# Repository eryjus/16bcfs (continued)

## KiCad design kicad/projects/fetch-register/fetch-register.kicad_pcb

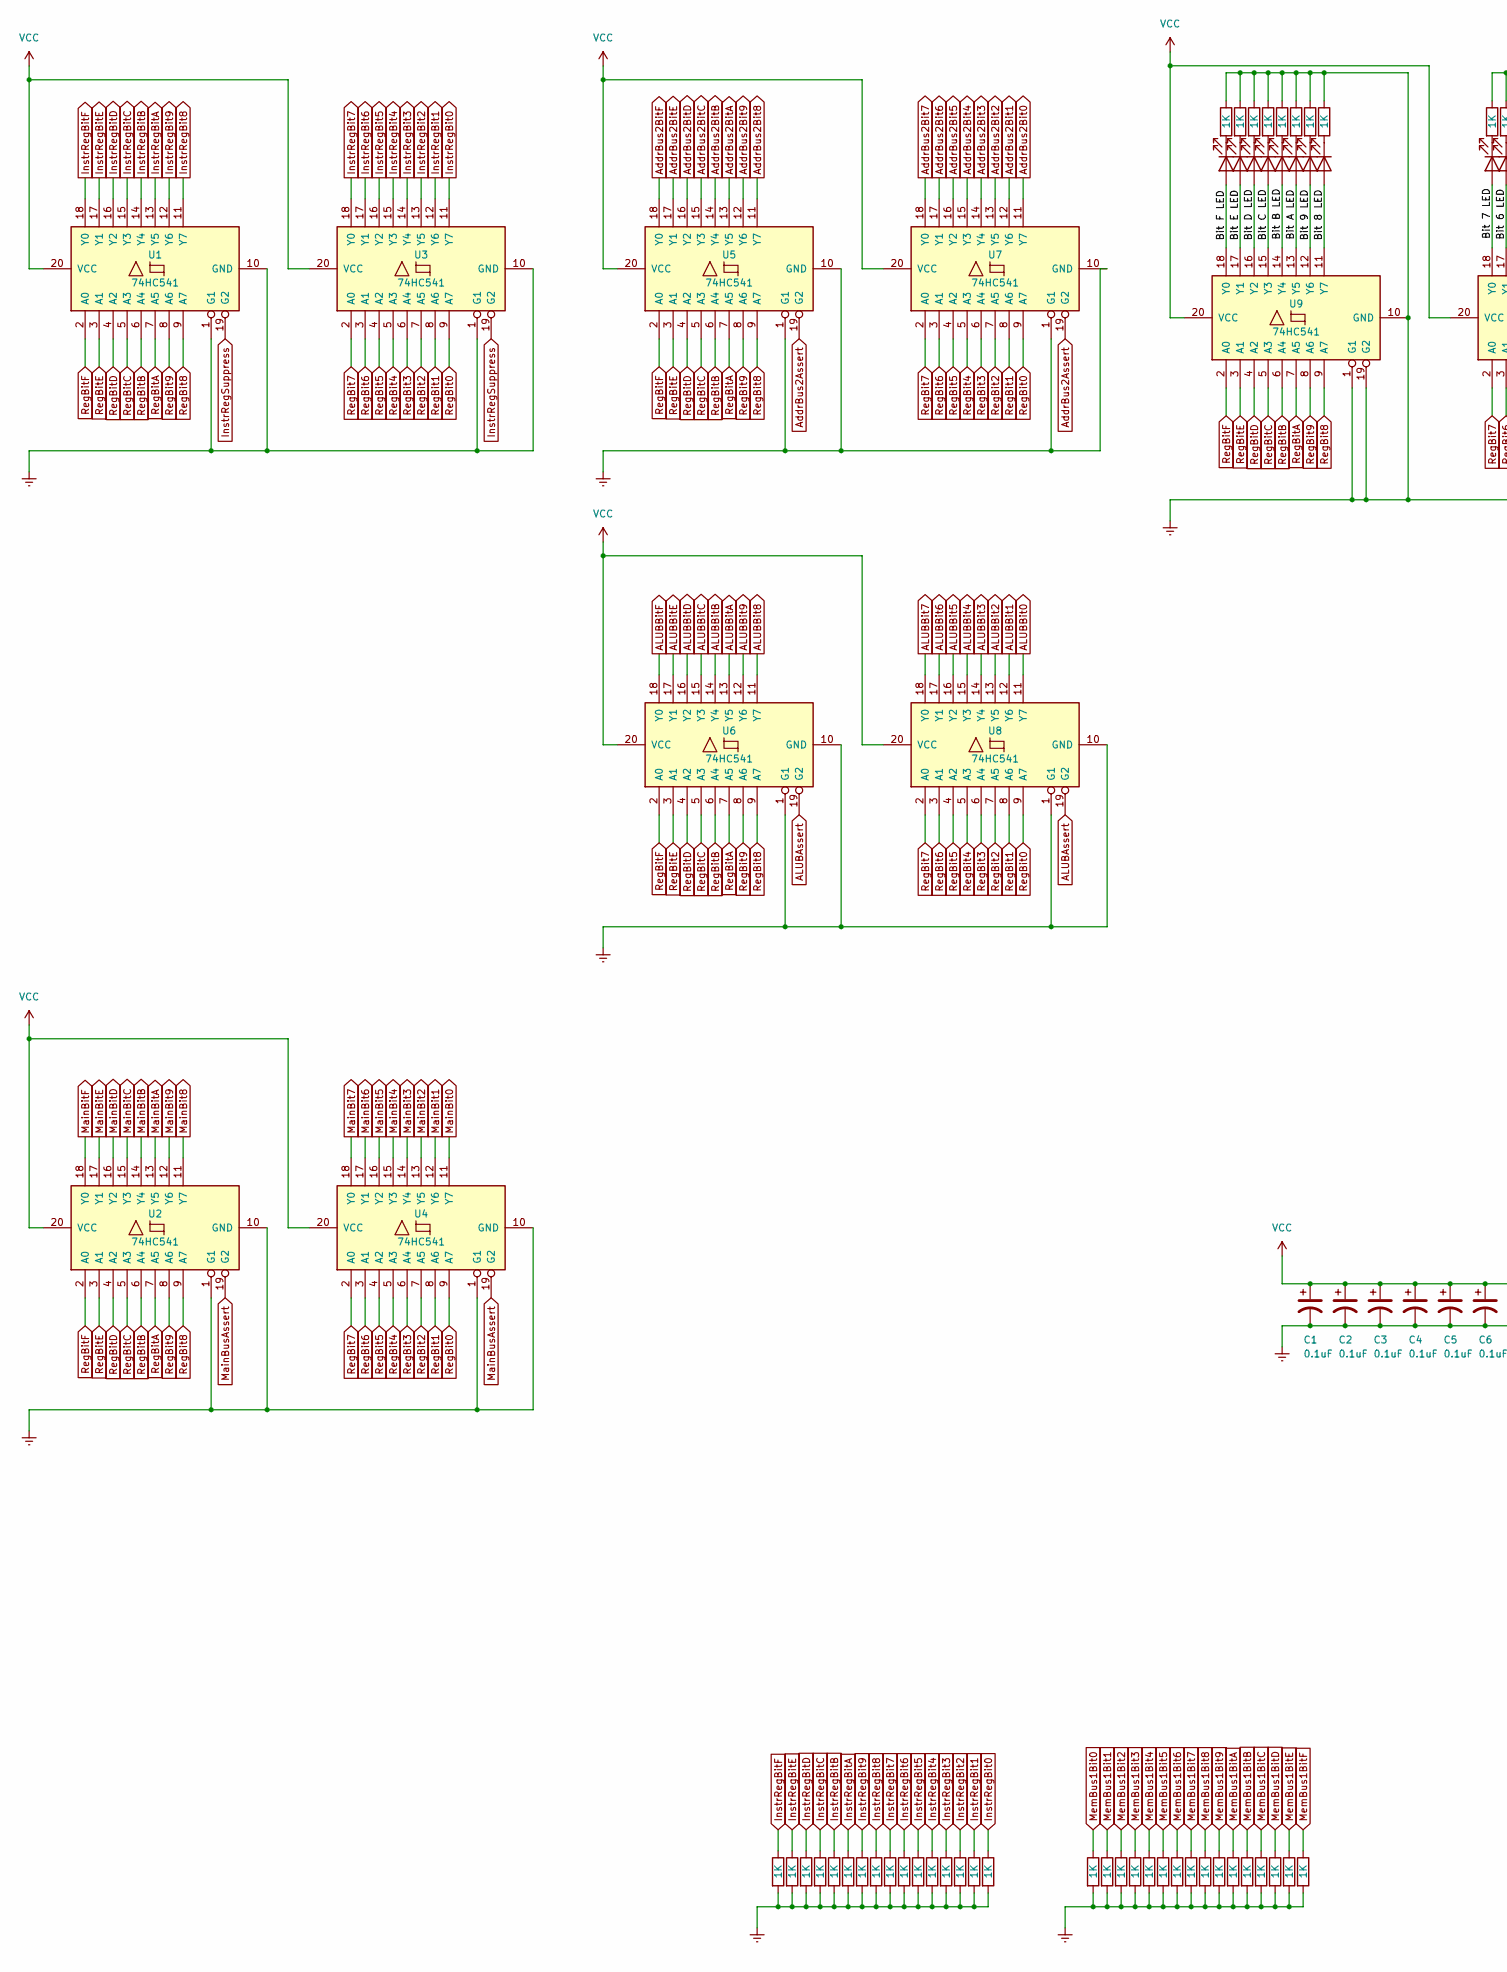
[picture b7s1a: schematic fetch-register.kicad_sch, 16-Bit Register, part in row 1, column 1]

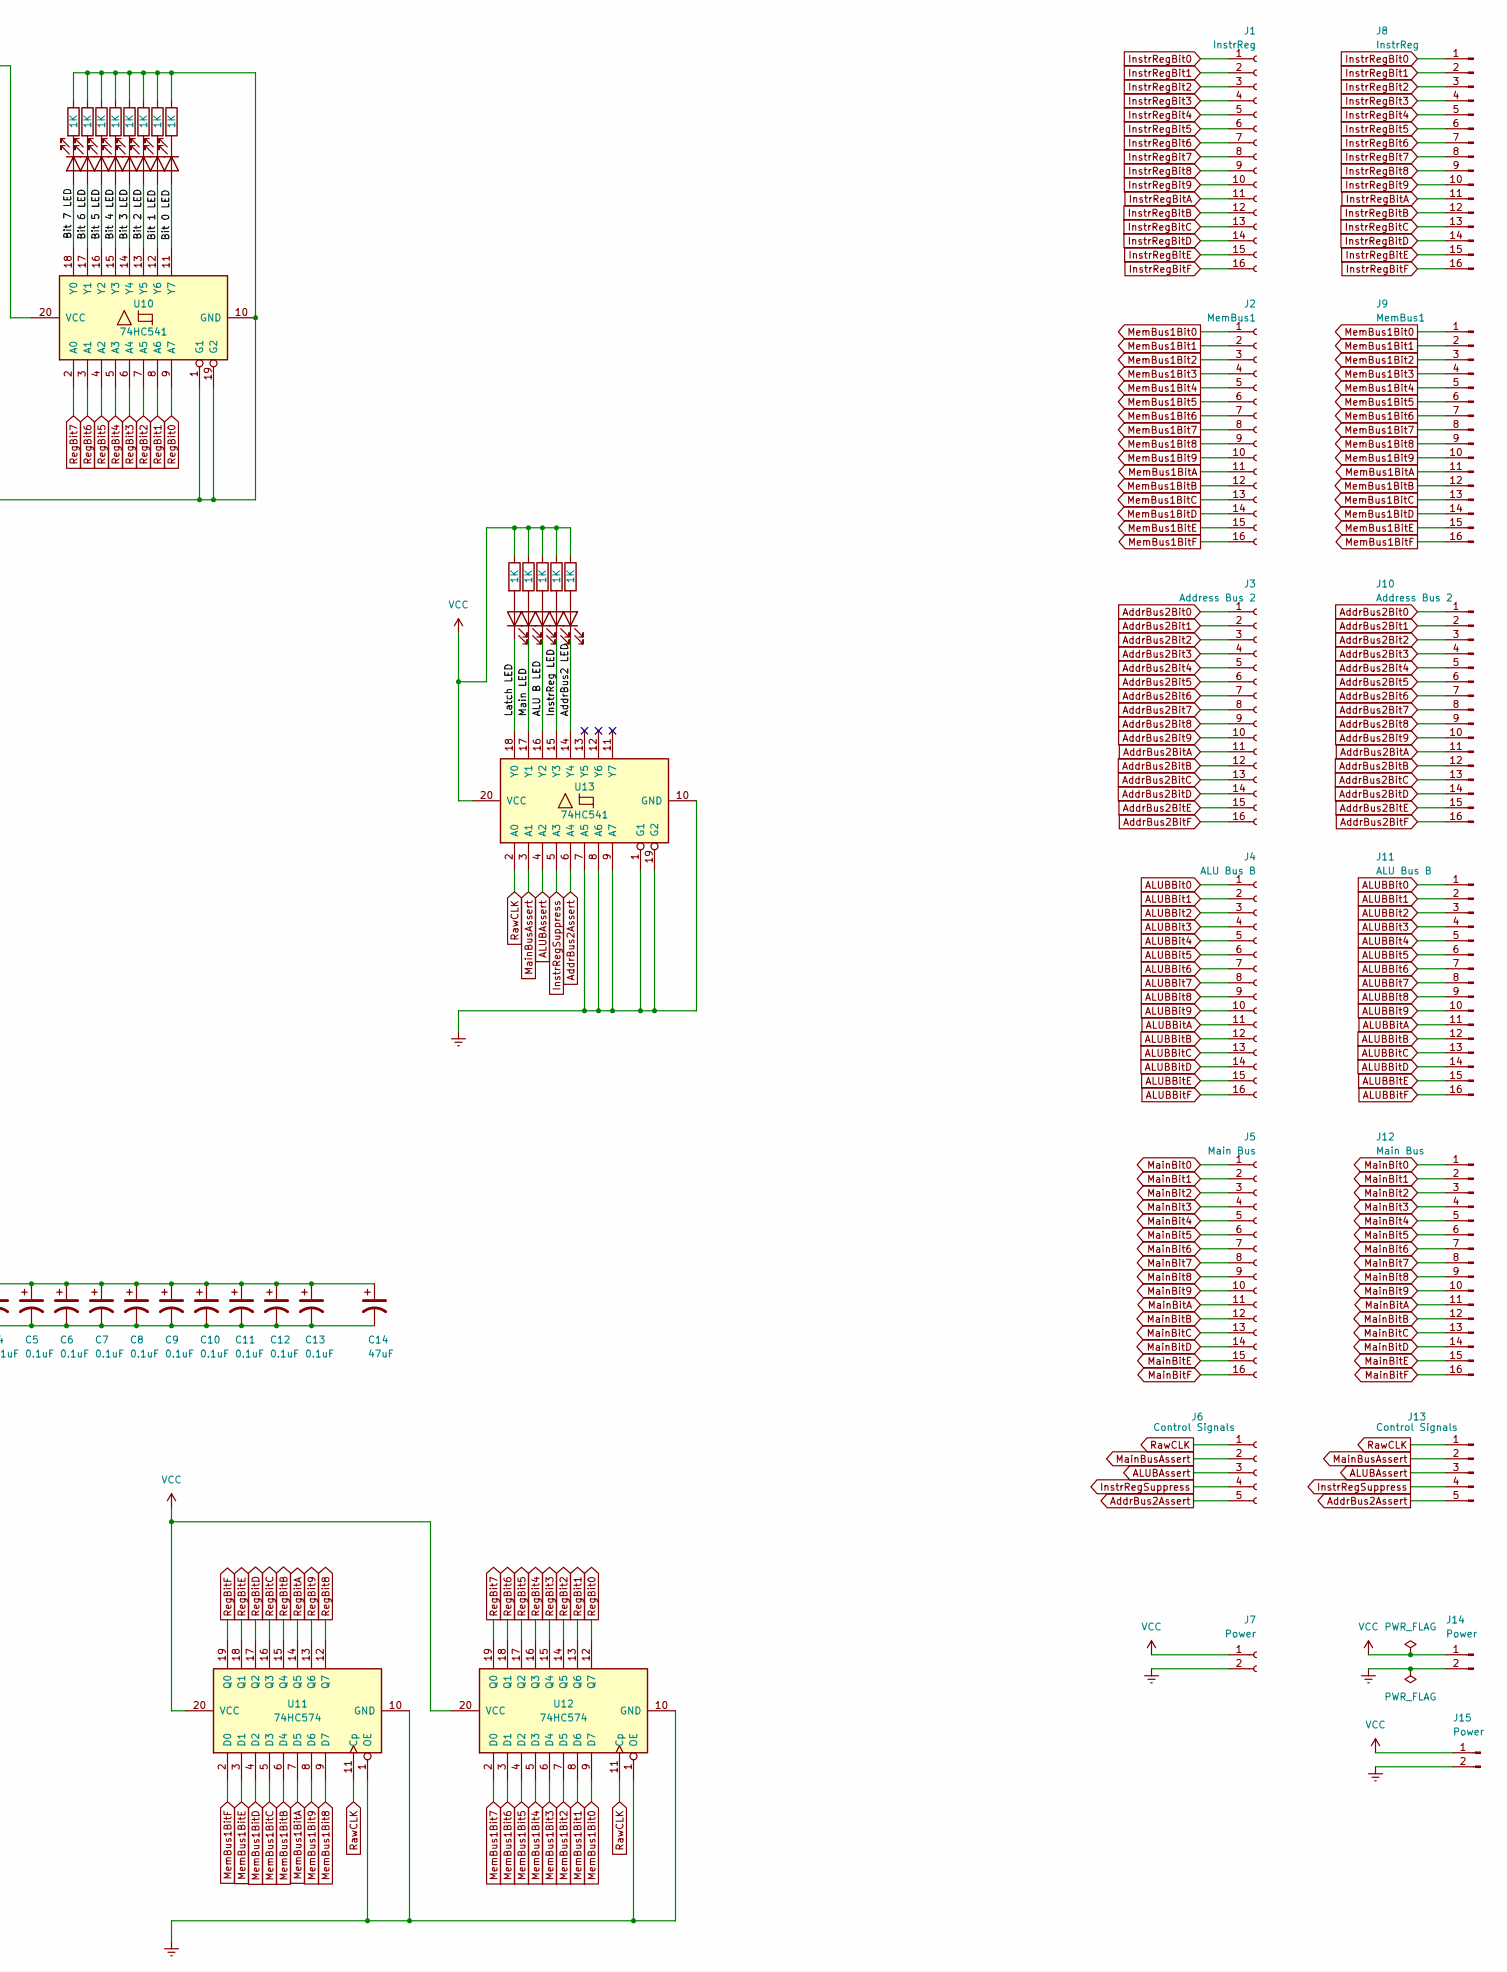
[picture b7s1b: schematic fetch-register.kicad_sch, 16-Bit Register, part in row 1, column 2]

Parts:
C1, C2, C3, C4, C5, C6, C7, C8, C9, C10, C11, C12, C13: 0.1uF; C_1206_3216Metric_Pad1.33x1.80mm_HandSolder
C14: 47uF; C_1206_3216Metric_Pad1.33x1.80mm_HandSolder
D1, D2, D3, D4, D5, D6, D7, D8, D9, D10, D11, D12, D13, D14, D15, D16: Green; LED_1206_3216Metric_Pad1.42x1.75mm_HandSolder
D17, D18, D19, D20, D21: Red; LED_1206_3216Metric_Pad1.42x1.75mm_HandSolder
J1: InstrReg; PinSocket_1x16_P2.54mm_Vertical
J2: MemBus1; PinSocket_1x16_P2.54mm_Vertical
J3: Address Bus 2; PinSocket_1x16_P2.54mm_Vertical
J4: ALU Bus B; PinSocket_1x16_P2.54mm_Vertical
J5: Main Bus; PinSocket_1x16_P2.54mm_Vertical
J6: Control Signals; PinSocket_1x05_P2.54mm_Vertical
J7: Power; PinSocket_1x02_P2.54mm_Vertical
J8: InstrReg; PinHeader_1x16_P2.54mm_Vertical
J9: MemBus1; PinHeader_1x16_P2.54mm_Vertical
J10: Address Bus 2; PinHeader_1x16_P2.54mm_Vertical
J11: ALU Bus B; PinHeader_1x16_P2.54mm_Vertical
J12: Main Bus; PinHeader_1x16_P2.54mm_Vertical
J13: Control Signals; PinHeader_1x05_P2.54mm_Vertical
J14, J15: Power; PinHeader_1x02_P2.54mm_Vertical
R1, R2, R3, R4, R5, R6, R7, R8, R9, R10, R11, R12, R13, R14, R15, R16, R17, R18, R19, R20, R21, R22, R23, R24, R25, R26, R27, R28, R29, R30, R31, R32, R33, R34, R35, R36, R37, R38, R39, R40, R41, R42, R43, R44, R45, R46, R47, R48, R49, R50, R51, R52, R53: 1K; R_1206_3216Metric_Pad1.30x1.75mm_HandSolder
U1, U2, U3, U4, U5, U6, U7, U8, U9, U10, U13: 74HC541; SOIC-20W_7.5x12.8mm_P1.27mm
U11, U12: 74HC574; SOIC-20W_7.5x12.8mm_P1.27mm

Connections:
/ALU B LED: D19.1 (K), U13.16 (Y2)
/AddrBus2 LED: D21.1 (K), U13.14 (Y4)
/Bit 0 LED: D16.2 (A), U10.11 (Y7)
/Bit 1 LED: D15.2 (A), U10.12 (Y6)
/Bit 2 LED: D14.2 (A), U10.13 (Y5)
/Bit 3 LED: D13.2 (A), U10.14 (Y4)
/Bit 4 LED: D12.2 (A), U10.15 (Y3)
/Bit 5 LED: D11.2 (A), U10.16 (Y2)
/Bit 6 LED: D10.2 (A), U10.17 (Y1)
/Bit 7 LED: D9.2 (A), U10.18 (Y0)
/Bit 8 LED: D8.2 (A), U9.11 (Y7)
/Bit 9 LED: D7.2 (A), U9.12 (Y6)
/Bit A LED: D6.2 (A), U9.13 (Y5)
/Bit B LED: D5.2 (A), U9.14 (Y4)
/Bit C LED: D4.2 (A), U9.15 (Y3)
/Bit D LED: D3.2 (A), U9.16 (Y2)
/Bit E LED: D2.2 (A), U9.17 (Y1)
/Bit F LED: D1.2 (A), U9.18 (Y0)
/InstrReg LED: D20.1 (K), U13.15 (Y3)
/Latch LED: D17.1 (K), U13.18 (Y0)
/Main LED: D18.1 (K), U13.17 (Y1)
ALUBAssert: J6.3, J13.3, U6.19 (G2), U8.19 (G2), U13.4 (A2)
ALUBBit0: J4.1, J11.1, U8.11 (Y7)
ALUBBit1: J4.2, J11.2, U8.12 (Y6)
ALUBBit2: J4.3, J11.3, U8.13 (Y5)
ALUBBit3: J4.4, J11.4, U8.14 (Y4)
ALUBBit4: J4.5, J11.5, U8.15 (Y3)
ALUBBit5: J4.6, J11.6, U8.16 (Y2)
ALUBBit6: J4.7, J11.7, U8.17 (Y1)
ALUBBit7: J4.8, J11.8, U8.18 (Y0)
ALUBBit8: J4.9, J11.9, U6.11 (Y7)
ALUBBit9: J4.10, J11.10, U6.12 (Y6)
ALUBBitA: J4.11, J11.11, U6.13 (Y5)
ALUBBitB: J4.12, J11.12, U6.14 (Y4)
ALUBBitC: J4.13, J11.13, U6.15 (Y3)
ALUBBitD: J4.14, J11.14, U6.16 (Y2)
ALUBBitE: J4.15, J11.15, U6.17 (Y1)
ALUBBitF: J4.16, J11.16, U6.18 (Y0)
AddrBus2Assert: J6.5, J13.5, U5.19 (G2), U7.19 (G2), U13.6 (A4)
AddrBus2Bit0: J3.1, J10.1, U7.11 (Y7)
AddrBus2Bit1: J3.2, J10.2, U7.12 (Y6)
AddrBus2Bit2: J3.3, J10.3, U7.13 (Y5)
AddrBus2Bit3: J3.4, J10.4, U7.14 (Y4)
AddrBus2Bit4: J3.5, J10.5, U7.15 (Y3)
AddrBus2Bit5: J3.6, J10.6, U7.16 (Y2)
AddrBus2Bit6: J3.7, J10.7, U7.17 (Y1)
AddrBus2Bit7: J3.8, J10.8, U7.18 (Y0)
AddrBus2Bit8: J3.9, J10.9, U5.11 (Y7)
AddrBus2Bit9: J3.10, J10.10, U5.12 (Y6)
AddrBus2BitA: J3.11, J10.11, U5.13 (Y5)
AddrBus2BitB: J3.12, J10.12, U5.14 (Y4)
AddrBus2BitC: J3.13, J10.13, U5.15 (Y3)
AddrBus2BitD: J3.14, J10.14, U5.16 (Y2)
AddrBus2BitE: J3.15, J10.15, U5.17 (Y1)
AddrBus2BitF: J3.16, J10.16, U5.18 (Y0)
GNDREF: C1.2, C2.2, C3.2, C4.2, C5.2, C6.2, C7.2, C8.2, C9.2, C10.2, C11.2, C12.2, C13.2, C14.2, J7.2, J14.2, J15.2, R1.2, R2.2, R3.2, R4.2, R5.2, R6.2, R7.2, R8.2, R9.2, R10.2, R11.2, R12.2, R13.2, R14.2, R15.2, R16.2, R17.2, R18.2, R19.2, R20.2, R21.2, R22.2, R23.2, R24.2, R25.2, R26.2, R27.1, R28.2, R29.1, R30.2, R31.1, R32.2, R33.1, R34.2, R35.1, R36.2, R37.1, R38.2, R39.1, R40.1, R41.1, R42.1, R43.1, R44.1, R45.1, R46.1, R47.1, R48.1, U1.1 (G1), U1.10 (GND), U2.1 (G1), U2.10 (GND), U3.1 (G1), U3.10 (GND), U4.1 (G1), U4.10 (GND), U5.1 (G1), U5.10 (GND), U6.1 (G1), U6.10 (GND), U7.1 (G1), U7.10 (GND), U8.1 (G1), U8.10 (GND), U9.1 (G1), U9.10 (GND), U9.19 (G2), U10.1 (G1), U10.10 (GND), U10.19 (G2), U11.1 (OE), U11.10 (GND), U12.1 (OE), U12.10 (GND), U13.1 (G1), U13.7 (A5), U13.8 (A6), U13.9 (A7), U13.10 (GND), U13.19 (G2)
InstrRegBit0: J1.1, J8.1, R16.1, U3.11 (Y7)
InstrRegBit1: J1.2, J8.2, R15.1, U3.12 (Y6)
InstrRegBit2: J1.3, J8.3, R14.1, U3.13 (Y5)
InstrRegBit3: J1.4, J8.4, R13.1, U3.14 (Y4)
InstrRegBit4: J1.5, J8.5, R12.1, U3.15 (Y3)
InstrRegBit5: J1.6, J8.6, R11.1, U3.16 (Y2)
InstrRegBit6: J1.7, J8.7, R10.1, U3.17 (Y1)
InstrRegBit7: J1.8, J8.8, R9.1, U3.18 (Y0)
InstrRegBit8: J1.9, J8.9, R8.1, U1.11 (Y7)
InstrRegBit9: J1.10, J8.10, R7.1, U1.12 (Y6)
InstrRegBitA: J1.11, J8.11, R6.1, U1.13 (Y5)
InstrRegBitB: J1.12, J8.12, R5.1, U1.14 (Y4)
InstrRegBitC: J1.13, J8.13, R4.1, U1.15 (Y3)
InstrRegBitD: J1.14, J8.14, R3.1, U1.16 (Y2)
InstrRegBitE: J1.15, J8.15, R2.1, U1.17 (Y1)
InstrRegBitF: J1.16, J8.16, R1.1, U1.18 (Y0)
InstrRegSuppress: J6.4, J13.4, U1.19 (G2), U3.19 (G2), U13.5 (A3)
MainBit0: J5.1, J12.1, U4.11 (Y7)
MainBit1: J5.2, J12.2, U4.12 (Y6)
MainBit2: J5.3, J12.3, U4.13 (Y5)
MainBit3: J5.4, J12.4, U4.14 (Y4)
MainBit4: J5.5, J12.5, U4.15 (Y3)
MainBit5: J5.6, J12.6, U4.16 (Y2)
MainBit6: J5.7, J12.7, U4.17 (Y1)
MainBit7: J5.8, J12.8, U4.18 (Y0)
MainBit8: J5.9, J12.9, U2.11 (Y7)
MainBit9: J5.10, J12.10, U2.12 (Y6)
MainBitA: J5.11, J12.11, U2.13 (Y5)
MainBitB: J5.12, J12.12, U2.14 (Y4)
MainBitC: J5.13, J12.13, U2.15 (Y3)
MainBitD: J5.14, J12.14, U2.16 (Y2)
MainBitE: J5.15, J12.15, U2.17 (Y1)
MainBitF: J5.16, J12.16, U2.18 (Y0)
MainBusAssert: J6.2, J13.2, U2.19 (G2), U4.19 (G2), U13.3 (A1)
MemBus1Bit0: J2.1, J9.1, R17.1, U12.9 (D7)
MemBus1Bit1: J2.2, J9.2, R18.1, U12.8 (D6)
MemBus1Bit2: J2.3, J9.3, R19.1, U12.7 (D5)
MemBus1Bit3: J2.4, J9.4, R20.1, U12.6 (D4)
MemBus1Bit4: J2.5, J9.5, R21.1, U12.5 (D3)
MemBus1Bit5: J2.6, J9.6, R22.1, U12.4 (D2)
MemBus1Bit6: J2.7, J9.7, R23.1, U12.3 (D1)
MemBus1Bit7: J2.8, J9.8, R24.1, U12.2 (D0)
MemBus1Bit8: J2.9, J9.9, R25.1, U11.9 (D7)
MemBus1Bit9: J2.10, J9.10, R26.1, U11.8 (D6)
MemBus1BitA: J2.11, J9.11, R28.1, U11.7 (D5)
MemBus1BitB: J2.12, J9.12, R30.1, U11.6 (D4)
MemBus1BitC: J2.13, J9.13, R32.1, U11.5 (D3)
MemBus1BitD: J2.14, J9.14, R34.1, U11.4 (D2)
MemBus1BitE: J2.15, J9.15, R36.1, U11.3 (D1)
MemBus1BitF: J2.16, J9.16, R38.1, U11.2 (D0)
unnamed: D1.1 (K), R27.2
unnamed: D2.1 (K), R29.2
unnamed: D3.1 (K), R31.2
unnamed: D4.1 (K), R33.2
unnamed: D5.1 (K), R35.2
unnamed: D6.1 (K), R37.2
unnamed: D7.1 (K), R39.2
unnamed: D8.1 (K), R40.2
unnamed: D9.1 (K), R41.2
unnamed: D10.1 (K), R42.2
unnamed: D11.1 (K), R43.2
unnamed: D12.1 (K), R44.2
unnamed: D13.1 (K), R45.2
unnamed: D14.1 (K), R46.2
unnamed: D15.1 (K), R47.2
unnamed: D16.1 (K), R48.2
unnamed: D17.2 (A), R49.2
unnamed: D18.2 (A), R50.2
unnamed: D19.2 (A), R51.2
unnamed: D20.2 (A), R52.2
unnamed: D21.2 (A), R53.2
RawCLK: J6.1, J13.1, U11.11 (Cp), U12.11 (Cp), U13.2 (A0)
RegBit0: U3.9 (A7), U4.9 (A7), U7.9 (A7), U8.9 (A7), U10.9 (A7), U12.12 (Q7)
RegBit1: U3.8 (A6), U4.8 (A6), U7.8 (A6), U8.8 (A6), U10.8 (A6), U12.13 (Q6)
RegBit2: U3.7 (A5), U4.7 (A5), U7.7 (A5), U8.7 (A5), U10.7 (A5), U12.14 (Q5)
RegBit3: U3.6 (A4), U4.6 (A4), U7.6 (A4), U8.6 (A4), U10.6 (A4), U12.15 (Q4)
RegBit4: U3.5 (A3), U4.5 (A3), U7.5 (A3), U8.5 (A3), U10.5 (A3), U12.16 (Q3)
RegBit5: U3.4 (A2), U4.4 (A2), U7.4 (A2), U8.4 (A2), U10.4 (A2), U12.17 (Q2)
RegBit6: U3.3 (A1), U4.3 (A1), U7.3 (A1), U8.3 (A1), U10.3 (A1), U12.18 (Q1)
RegBit7: U3.2 (A0), U4.2 (A0), U7.2 (A0), U8.2 (A0), U10.2 (A0), U12.19 (Q0)
RegBit8: U1.9 (A7), U2.9 (A7), U5.9 (A7), U6.9 (A7), U9.9 (A7), U11.12 (Q7)
RegBit9: U1.8 (A6), U2.8 (A6), U5.8 (A6), U6.8 (A6), U9.8 (A6), U11.13 (Q6)
RegBitA: U1.7 (A5), U2.7 (A5), U5.7 (A5), U6.7 (A5), U9.7 (A5), U11.14 (Q5)
RegBitB: U1.6 (A4), U2.6 (A4), U5.6 (A4), U6.6 (A4), U9.6 (A4), U11.15 (Q4)
RegBitC: U1.5 (A3), U2.5 (A3), U5.5 (A3), U6.5 (A3), U9.5 (A3), U11.16 (Q3)
RegBitD: U1.4 (A2), U2.4 (A2), U5.4 (A2), U6.4 (A2), U9.4 (A2), U11.17 (Q2)
RegBitE: U1.3 (A1), U2.3 (A1), U5.3 (A1), U6.3 (A1), U9.3 (A1), U11.18 (Q1)
RegBitF: U1.2 (A0), U2.2 (A0), U5.2 (A0), U6.2 (A0), U9.2 (A0), U11.19 (Q0)
VCC: C1.1, C2.1, C3.1, C4.1, C5.1, C6.1, C7.1, C8.1, C9.1, C10.1, C11.1, C12.1, C13.1, C14.1, J7.1, J14.1, J15.1, R49.1, R50.1, R51.1, R52.1, R53.1, U1.20 (VCC), U2.20 (VCC), U3.20 (VCC), U4.20 (VCC), U5.20 (VCC), U6.20 (VCC), U7.20 (VCC), U8.20 (VCC), U9.20 (VCC), U10.20 (VCC), U11.20 (VCC), U12.20 (VCC), U13.20 (VCC)

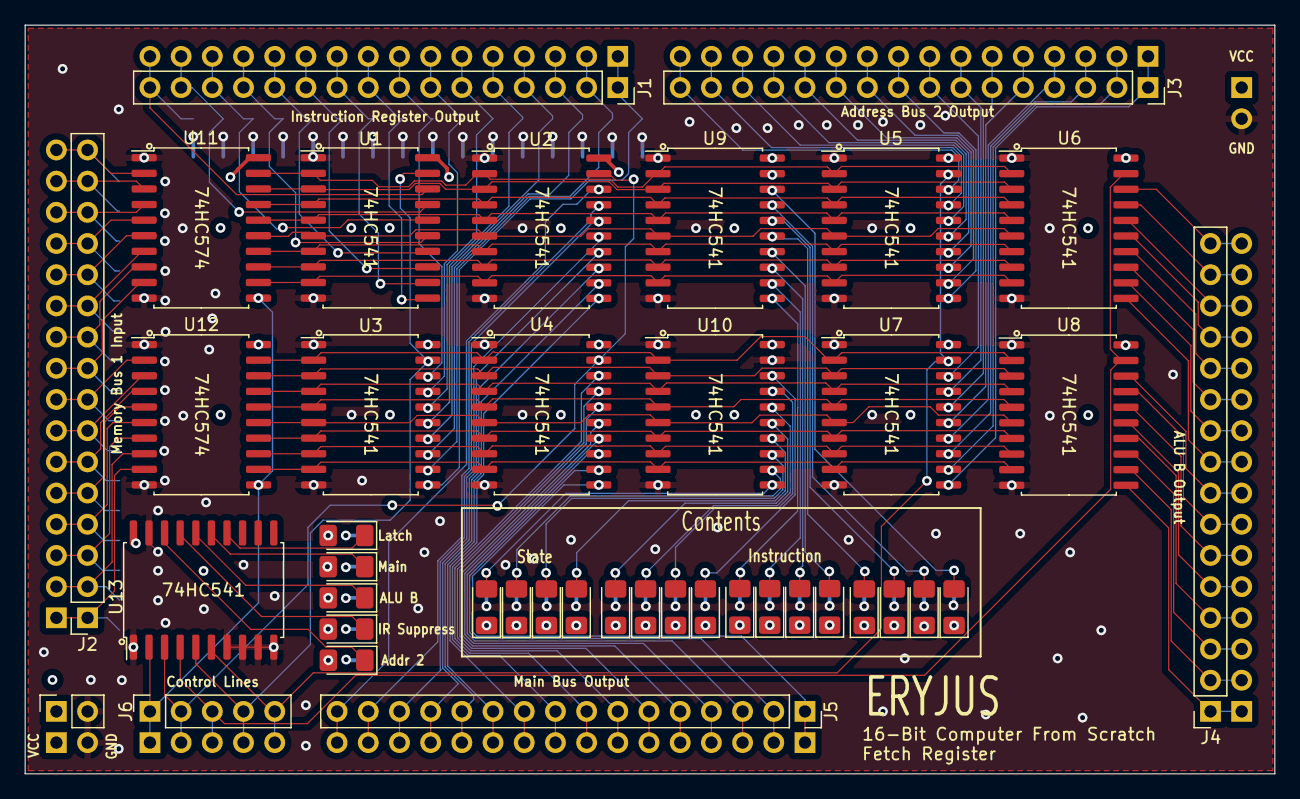
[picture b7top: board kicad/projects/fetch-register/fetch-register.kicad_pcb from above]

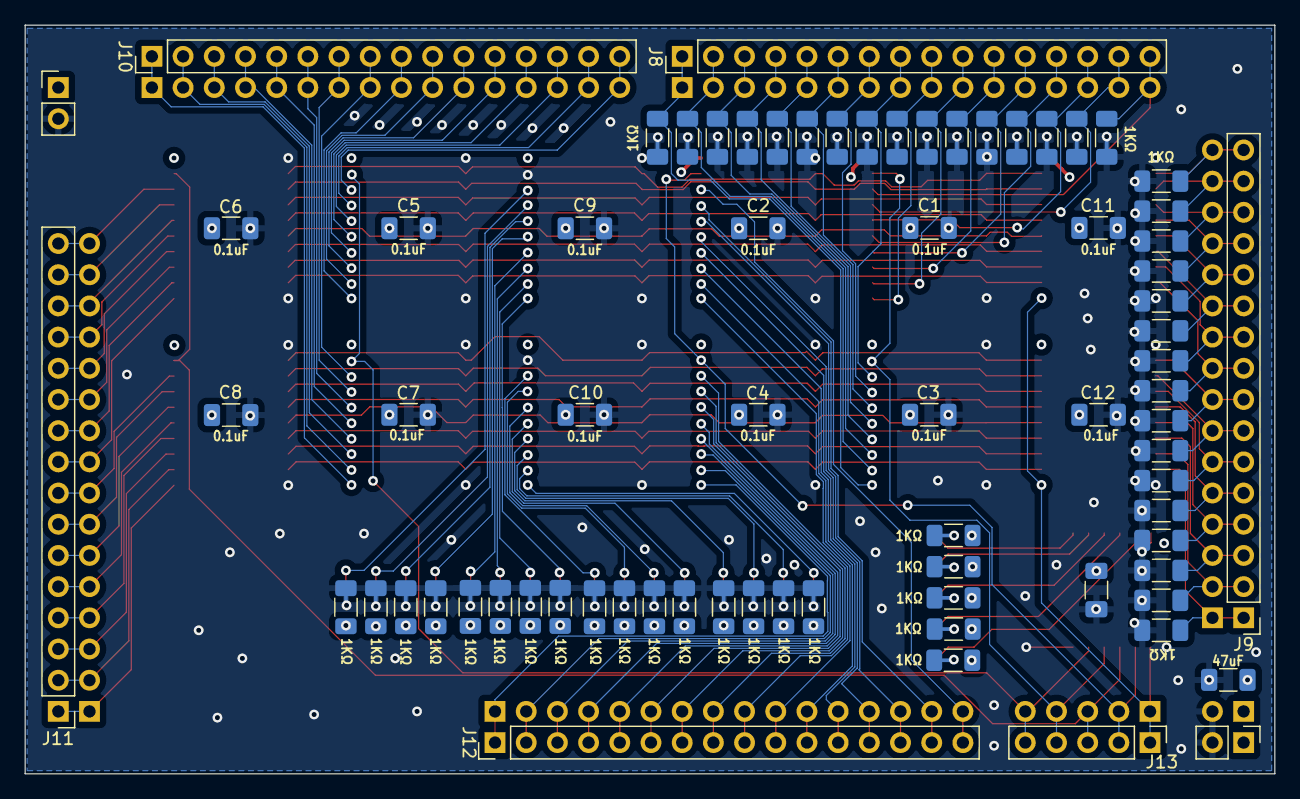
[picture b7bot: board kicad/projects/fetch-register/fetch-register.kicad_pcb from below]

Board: 4 copper layers, 101.8 x 61.0 mm, 116 parts (75 on the bottom side), 145 nets.

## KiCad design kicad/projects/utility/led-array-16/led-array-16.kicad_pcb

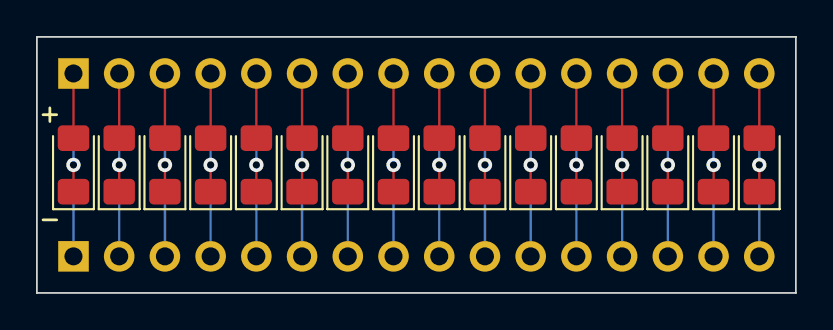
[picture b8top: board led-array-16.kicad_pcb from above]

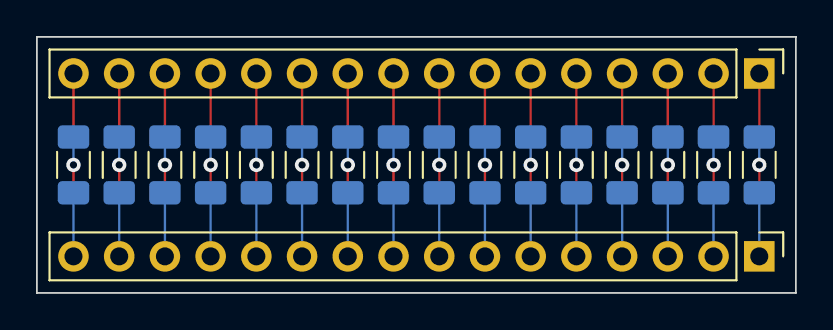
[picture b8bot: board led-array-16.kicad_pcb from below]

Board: 2 copper layers, 42.2 x 14.2 mm, 34 parts (18 on the bottom side), 48 nets.

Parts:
D1, D2, D3, D4, D5, D6, D7, D8, D9, D10, D11, D12, D13, D14, D15, D16: LED; LED_1206_3216Metric_Pad1.42x1.75mm_HandSolder
J1, J2: Conn_01x16_Pin; PinHeader_1x16_P2.54mm_Vertical
R1, R2, R3, R4, R5, R6, R7, R8, R9, R10, R11, R12, R13, R14, R15, R16: R; R_1206_3216Metric_Pad1.30x1.75mm_HandSolder

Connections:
unnamed: D1.2 (A), J1.1
unnamed: D1.1 (K), R1.1
unnamed: D2.2 (A), J1.2
unnamed: D2.1 (K), R2.1
unnamed: D3.2 (A), J1.3
unnamed: D3.1 (K), R3.1
unnamed: D4.2 (A), J1.4
unnamed: D4.1 (K), R4.1
unnamed: D5.2 (A), J1.5
unnamed: D5.1 (K), R5.1
unnamed: D6.2 (A), J1.6
unnamed: D6.1 (K), R6.1
unnamed: D7.2 (A), J1.7
unnamed: D7.1 (K), R7.1
unnamed: D8.2 (A), J1.8
unnamed: D8.1 (K), R8.1
unnamed: D9.2 (A), J1.9
unnamed: D9.1 (K), R9.1
unnamed: D10.2 (A), J1.10
unnamed: D10.1 (K), R10.1
unnamed: D11.2 (A), J1.11
unnamed: D11.1 (K), R11.1
unnamed: D12.2 (A), J1.12
unnamed: D12.1 (K), R12.1
unnamed: D13.2 (A), J1.13
unnamed: D13.1 (K), R13.1
unnamed: D14.2 (A), J1.14
unnamed: D14.1 (K), R14.1
unnamed: D15.2 (A), J1.15
unnamed: D15.1 (K), R15.1
unnamed: D16.2 (A), J1.16
unnamed: D16.1 (K), R16.1
unnamed: J2.1, R1.2
unnamed: J2.2, R2.2
unnamed: J2.3, R3.2
unnamed: J2.4, R4.2
unnamed: J2.5, R5.2
unnamed: J2.6, R6.2
unnamed: J2.7, R7.2
unnamed: J2.8, R8.2
unnamed: J2.9, R9.2
unnamed: J2.10, R10.2
unnamed: J2.11, R11.2
unnamed: J2.12, R12.2
unnamed: J2.13, R13.2
unnamed: J2.14, R14.2
unnamed: J2.15, R15.2
unnamed: J2.16, R16.2

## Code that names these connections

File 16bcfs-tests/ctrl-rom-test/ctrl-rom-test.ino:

//===================================================================================================================
//  ctrl-rom-test.ino -- Using an ESP32, perform tests on the EEPROM
//
//  Ok, here is a list of pins I need in order to implement this test:
//  ------------------------------------------------------------------
//   0-14:  These are the address pins for the SRAM
//  15-16:  Rx/Tx pins for the serial port
//     17:  Clock for latching the SRAM contents for review
//  18-25:  The 8-bit payload
//     26:  Reset hold
//
//  Without testing each pin to confirm each can be used, the high water mark for the number of pins available is
//  25.  25 at best.  This circuit needs 27.
//
//  So, we need to use a shifter to shift some bits -- either in or out.  The best bang for the buck is to shift
//  out the address value to read.  This trades 15 pins for 3:
//  * shift clock
//  * data pin
//  * clear signal
//
//  The result is 15 pins required to make this circuit work.
//
//      Date     Tracker  Version  Description
//  -----------  -------  -------  ---------------------------------------------------------------------------------
//  2024-Mar-13  Initial  v0.0.1   Initial version
//
//===================================================================================================================


#include "incbin.h"


extern unsigned char ______control_logic_ctrl0_bin[];


//
// -- Which pins are relevant to us?  (by GPIO)
//    -----------------------------------------
#define BIT7 36       // input bit 7
#define BIT6 39       // input bit 6
#define BIT5 34       // input bit 5
#define BIT4 35       // input bit 4
#define BIT3 32       // input bit 3
#define BIT2 33       // input bit 2
#define BIT1 25       // input bit 1
#define BIT0 26       // input bit 0

#define RHLD 13       // Reset Hold input


//#define CLK  22       // Latch Clock Output
#define SHFT 18       // Shift Clock Output
#define ADDR 19       // Address Pin Output
#define CLR  21       // Shifter Clear Signal Output
#define RST  5        // Reset button
#define CLK  17       // The main clock


#define LED_BUILTIN 2


//
// -- Set up the ESP32
//    ----------------
void setup() {
  //
  // -- Set up the pins
  //    ---------------
  pinMode(BIT0, INPUT);
  pinMode(BIT1, INPUT);
  pinMode(BIT2, INPUT);
  pinMode(BIT3, INPUT);
  pinMode(BIT4, INPUT);
  pinMode(BIT5, INPUT);
  pinMode(BIT6, INPUT);
  pinMode(BIT7, INPUT);

  pinMode(RHLD, INPUT_PULLUP);      // use an internal pullup resistor since it's an open drain signal


  //
  // -- Initialize the outputs to LOW...  but recall that there is only 1 inverter in the 3v3 to 5v
  //    level shifter.  So, we need to be careful about inverting the signals in code as well.
  //    -------------------------------------------------------------------------------------------
  pinMode(LTCH, OUTPUT);
  digitalWrite(LTCH, HIGH);

  pinMode(SHFT, OUTPUT);
  digitalWrite(SHFT, HIGH);

  pinMode(ADDR, OUTPUT);
  digitalWrite(ADDR, HIGH);

  pinMode(CLR, OUTPUT);
  digitalWrite(CLR, HIGH);
  delay(10);
  digitalWrite(CLR, LOW);

  pinMode(RST, OUTPUT);
  digitalWrite(RST, LOW);

  pinMode(CLK, OUTPUT);
  digitalWrite(CLK, LOW);

  pinMode(LED_BUILTIN, OUTPUT);
  digitalWrite(LED_BUILTIN, LOW);



  //
  // -- Send a greeting
  //    ---------------
  delay(2000);
  Serial.begin(115200);
  Serial.println();
  Serial.println(F("Welcome to the EEPROM tester"));
  Serial.println(F("Ready to test"));

  delay(1);

  Serial.println(F("Press Enter to begin"));
  while (Serial.read() != '\n') {}
}



//
// -- For whatever we are at, read the byte from the standard
//    -------------------------------------------------------
byte getGoldenByte(long i) {
//  return pgm_read_byte(geepromData + i);
  return ______control_logic_ctrl0_bin[i];
}



//
// -- Read the resulting byte from the sram
//    -------------------------------------
byte readSram(void) {
  bool b7 = digitalRead(BIT7);
  bool b6 = digitalRead(BIT6);
  bool b5 = digitalRead(BIT5);
  bool b4 = digitalRead(BIT4);
  bool b3 = digitalRead(BIT3);
  bool b2 = digitalRead(BIT2);
  bool b1 = digitalRead(BIT1);
  bool b0 = digitalRead(BIT0);

  byte rv = (b7 ? 0x80 : 0) | (b6 ? 0x40 : 0) | (b5 ? 0x20 : 0) | (b4 ? 0x10 : 0) |
      (b3 ? 0x08 : 0) | (b2 ? 0x04 : 0) | (b1 ? 0x02 : 0) | (b0 ? 0x01 : 0);

  return rv;
}



//
// -- Check a byte identified by index i
//    ----------------------------------
bool checkByte(long i) {
  int addr = ~i;      // -- remember, the address needs to be inverted

  pinMode(CLR, OUTPUT);
  digitalWrite(CLR, HIGH);
  digitalWrite(ADDR, HIGH);
  delay(10);
  digitalWrite(CLR, LOW);

  for (int b = 0; b < 16; b ++) {
    int bit = addr & (1<<(15-b));

    digitalWrite(ADDR, (bit == 0) ? LOW : HIGH);
    digitalWrite(SHFT, LOW);
    delay(1);
    digitalWrite(SHFT, HIGH);
  }

  delay(1);
  digitalWrite(CLK, LOW);
  delay(1);
  digitalWrite(CLK, HIGH);
  delay(1);

//  while (Serial.read() != '\n') {}

  byte s = readSram();
  byte g = getGoldenByte(i);

  Serial.printf("Expected %02.2x ", g);
  Serial.printf("Read %02.2x\n", s);

  return (g ^ s) == 0;
}



//
// -- This code is executed once per iteration, prepeatedly
//    -----------------------------------------------------
void loop() {
  unsigned long counter = 0;
  unsigned long earlyStop = 0 * 9;
  unsigned long lateStop = ((32768 + 3 - 0) * 9) - 1;


  //
  // -- Execute a Reset Sequence
  //    ------------------------
  digitalWrite(RST, HIGH);
  Serial.println(F("In reset.  Press Enter to continue."));

  while (Serial.read() != '\n') {}

  digitalWrite(RST, LOW);
  delay(250);


  //
  // -- wait for the reset hold to come high -- as it will work on the real hardware
  //    ----------------------------------------------------------------------------
  Serial.println(F("Copying data from EEPROM to SRAM"));
  Serial.println(F("... waiting for #RHLD"));

  while (digitalRead(RHLD) == LOW) {
  #if 0

    if (counter < earlyStop || counter >= lateStop) {
      Serial.printf("%10.10ld: Enter for LOW CLK\n", counter);
      while (Serial.read() != '\n') {}
    }

    digitalWrite(CLK, HIGH);
    delay(1);

    if (counter < earlyStop || counter >= lateStop) {
      Serial.printf("%10.10ld: Enter for HIGH CLK\n", counter);
      while (Serial.read() != '\n') {}
    }

    digitalWrite(CLK, LOW);
    delay(1);
    counter ++;

#else

    delay(500);

#endif
  }

  //
  // -- turn on the LED to indicate testing
  //    -----------------------------------
  digitalWrite(LED_BUILTIN, HIGH);
  Serial.println(F("Copy complete!  Testing!"));
  delay(10);

//  while (Serial.read() != '\n') {}


  //
  // -- clear the shift registers
  //    -------------------------
  pinMode(CLR, OUTPUT);
  digitalWrite(CLR, HIGH);
  delay(10);
  digitalWrite(CLR, LOW);



  for (long i = 0; i < 32768; i ++) {
    //
    // -- output some status indicators
    //    -----------------------------
//    if (i % 0x100 == 0) {
      Serial.printf("  address 0x%04.4x ", i);
//    }


    //
    // -- check if failed and if so, flash the LED and do nothing else
    //    ------------------------------------------------------------
//    checkByte(i);
    if (checkByte(i) == false) {
      Serial.println(F("Test FAILED!!!"));
      Serial.print(F("   location ")); Serial.println(i);


      //
      // -- flashing LED forever
      //    --------------------
      while (true) {
        digitalWrite(LED_BUILTIN, LOW);
        delay(250);
        digitalWrite(LED_BUILTIN, HIGH);
        delay(250);
      }
    }
  }


  //
  // -- if we get here, everything worked
  //    ---------------------------------
  digitalWrite(LED_BUILTIN, LOW);
  Serial.println(F("Testing complete: SRAM is good"));
  delay(10);



  //
  // -- wait for another reset and then loop
  //    ------------------------------------
  while (digitalRead(RHLD) == HIGH) {
    delay(500);
  }
}

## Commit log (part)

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2023-11-05 Consolidate several repos into 1; initial commit on this repo
2023-11-10 Add foundations for a Bus and Sanity Checks
2023-11-19 Combine GUI and HW into single class
2023-11-19 Correct an issue with CODEOWNERS
2023-11-19 Update c-cpp.yml
    Add moc to the build
2023-11-20 Update c-cpp.yml
    Add some investigation steps
2023-11-20 Create ci-build workflow
2023-11-25 Update the clock to emulate properly
    - Fixes #1
    - Completes #3
    - Completes #5
    - Completes #9
    - Completes #8
    - Completes #15
2023-12-04 Add Register Module and update the Clock Module
    * Completes #13
    * Fixes #12
    * Completes #14
    * Completes #10
    * Completes #18
    * Fixes #22
2023-12-20 Create the Register Module Schematic
2023-12-26 Create tools for SPI EEPROM programming
2023-12-27 Clean up another error with gitignore for SPI-Client
2023-12-31 Add the ALU Flags to the Emulator
    * Closes #39
    * Closes #33
    * Closes #40
    * Closes #42
2023-12-31 Add the ALU Flags to the Emulator (#48)
    * Closes #39
    * Closes #33
    * Closes #40
    * Closes #42
2024-01-07 Complete the EEPROM programmer functionalities (#53)
    * Closes #43
    * Closes #44
    * Closed #45
    * Closes #46
    * Closes #47
2024-01-14 `.organization` architecture directive comes first
    This directive must come before any other architecture directive.
    Closes #62
2024-01-14 Asm update 001 (#66)
    * Convert all sources to c++
    This change is a brute-force move to c++ sources and some basic
    singleton classes with no change in functionality. Care was taken so
    that no new bugs were introduced. However, it might have happened.
    Note that several pre-existing bugs will be identified and added to the
    GutHub issues list.
2024-01-22 Create Foundation for Emulating EEPROM (#76)
    * Closes #67
    * Closes #69
    * Closes #70
    * Closes #71
2024-01-30 Create a Control ROM Control Circuit (#83)
    * Closes #72
    * Closes #77
    * Closes #79
    * Closes #80
    * Closes #82
2024-02-05 Add a Control ROM Control Circuit and Schematic
    * Closes #91
    * Closes #84
    * Closes #85
    * Closes #86
    * Closes #68
    * Closes #88
2024-02-05 Update ERC to ignore spice model issues
2024-02-17 Complete the EEPROM to SRAM copy for the Emulator
    * Closes #78
    * Closes #32
    * Closes #93
    * Starts #97
    * Closes #81
    * Closes #100
2024-02-27 Fix 74xx03 to NAND; Some additional minor corrections (#106)
    * Fixes #104
    * Closes #105
    * Closes #99
    * Closes #87
    * Defers #94
    * Defers #95
2024-02-27 Video 0093 (#112)
    * Fix 74xx03 to NAND; Some additional minor corrections
    * Fixes #104
    * Closes #105
    * Closes #99
    * Closes #87
    * Defers #94
2024-03-12 Create and Integrate a Control ROM Module (#116)
    * Fixes #108
    * Closes #109
    * Closes #110
    * Closes #111
    * Closes #114
    * Closes #115
2024-03-19 BUild a Test Rig to Confirm the EEPROM copy to SRAM
    * Starts #118
    * Closes #117
2024-03-31 Control ROM PCB Layout
    * Closes #118
    * Fixes #126
    * Fixes #127
    * Closes #128
    * Closes #129
    * Starts #119
2024-04-27 Control ROM Control Cleanup
    * Closes #123
    * Closes #132
    * Completes #119
    * Defers #89
    * Defers #122
    * Defers #121
2024-04-28 Add IC documentation
2024-04-30 Reorganize the Control Word
    * Closes #136
2024-05-01 Add all 16 EEPROM to the emulator
    * Closes #137
2024-05-03 Create 3-, 4-, and 7-bit demultiplexer sub-modules
    * Closes #139
2024-05-05 Update the directive prefixes to be '.', ':', or '%' as appropriate.
2024-05-05 Change the Assembler comments to start with '//'
    * Closes #142
    * Closes #63
    * Closes #65
2024-05-09 Correct an issue with the assembler error formatting
2024-05-09 Video 0098 (#146)
    Add Signal De-Multiplexing:
    * Create 3-, 4-, and 7-bit demultiplexer sub-modules
    * Add IC documentation
    * Create the new 74xx238 IC for the emulator
    * Reorganize the Control Word
    * Make the EEPROM copy to SRAM optionally pedantic or quick
2024-05-16 Corrections to free-run the emulator with NOPs
2024-05-17 Clean up some remaining comments
2024-06-07 Complete the Control Logic Mid-Plane PCB Design
    * Completes #148
    * Completes #120
    * Completes #121
    * Closes #145
    * Closes #41
    * Closes #35
2024-06-07 Correct Silkscreen on the Control ROM Module
    The Control ROM Module did not have a correct silkscreen and that needed
    to be corrected prior to ordering the PCBs. This commit handles this
    fix.
2024-06-09 Clean up the UI
    This commit cleans up the user interface for the emulator. Nothing more
    has been tested.
2024-06-09 Fix an issue with the Fetch Register Clock
    First the clock signal was not being routed to the Fetch Register. This
    was quickly resolved.
    Then, the Instruction Suppress signal really needs to be inverted before
    it is ANDed with the clock. This was sinply forgotten as I had it in my
    notes to make this happen. This was also quickly corrected.
    The clock is now working, latching the signals on Address Bus 1, which
2024-06-09 Commit a change the the KiCad proejct files
    THis change was a tickle from opening and reviewing the Fetch Register.
    It is simple a maintenance commit, which will be reviewed and updated
    with a subsequent commit.
2024-06-09 Fix the name of the bus with multiple asserts
    The code was properly detecting that multiple things were asserting onto
    a bus, but had no knowledge of that bus's name.
    This fix addresses this by requiring a name of a bus to be specified
    when creating the bus, and then passing that name to `SetObjectName()`.
    Of course, this was not a defaulted parameter for Bus creation, so every
    instance had to be modified to address this concern.
2024-06-09 Correct an issue with the Control ROM Control Mod
    The Control ROM Control Module MUXes in the emulator were all tied to
    the least significant nibble on the instruction coming from the
    instruction register.
    This is obviously not correct.
    This commit updates the Control ROM Control Module to properly
    distribute those signals so that each MUX input pin has its own unique
2024-06-10 Fix the Control ROM always having signals on
    This was caused by the SRAM (AS6C62256 IC) not signaling the updates
    properly for all changes in output. To overcome this, the code was
    changed to update all outputs and signal that every line changed.
    This also had the effect of cleaning up the concern that a NOP was not
    asserted when the Instruction Suppress signal was asserted.
    Some additional debug code was found and removed for clarity.
2024-06-10 Move Ctrl ROM LEDs after the Latch
    This change moves the LED to be driven after the Latch whereas it was
    before the latch prior. Somewhere along the line, the pedantic copy
    broke. I was not testing that with each commit.
2024-06-10 Remove the testing rig for the Fetch Register
    Complete the change to the Fetch Register by creating an
    InstructionInBus, renaming the Insutrction Bus to be the
    InstructionOutBus, and removing all the testing harness code.
2024-06-11 Draft a first update to the Fetch Reg Schematic
    Here I take a first cut at updating the the Fetch Register Schematic.
    No checks have been completed, just component renames and reductions.
    A complete audit against the code is still required.
2024-06-12 Update the Fetch Register Schematics
    This commit updates the Fetch Register Schematics to reflect the new
    design. As far as I can tell at the time of this commit, all changes
    are properly reflected and no other changes are expected, except maybe
    adding a test point or 2 as the situation on the PCB dictates.
2024-06-13 Collapse and Organize the left of the PCB
    The left side of the PCB was organized with this commit. It is reduced
    in height by about 1/4 to 1/3. This than sets the desired height for
    the entire PCB.
2024-06-13 Add 0R Resistors and Test Points to the PCB
    Get this done before routing the PCB
2024-06-14 Complete the silkscreen on the Fetch Register
    This commit completed the silkscreen for the fetch register.
    Overall, this is the completion of the Fetch Register design and PCB
    layout.
2024-06-15 Change to a precompiled header
    Closes #155
2024-06-18 Create an Instruction Register
    The insturction register is created as a simple bus observer with LEDs
    to display the contents. The contents are latched at the proper time
    and therefore displayed for an entire clock cycle, locking the value at
    the rising edge.
2024-06-20 Complete the Schematic and PCB designs
    This commit:
    * Closes #160
    * Closes #161
    The Schematic and PCB design are both complete.
2024-08-20 Create a Program ROM Module
    This commit creates a Program ROM Module and loads the contents from
    disk. With this commit, there are concerns with the Control ROM Control
    Module LEDs, which still need to be addressed. Overall the Program ROM
    Module appears to work properly.
2024-08-24 Update all connect() calls to also check for Unique
2024-08-24 Fix an issue with loading the GP-Reg with a value
    This commit fixes a problem when loading the General-Purpose Register
    with a value. There were multiple conditions creating a problem, which
    include not properly asserting onto the main bus.
2024-11-03 Create the Reset Module and (mostly) debug it
2024-11-05 Added some debugging code
    This is still not working. I will need to revamp the reset routines for
    the emulator to get this to work properly. Everything will need an
    initial state on construction and a `reset()` routine to place
    everything into a proper state. This in itself will be a major change.
2024-11-09 Make a number of changes to the schematic and emulator
    These changes are incremental to getting the emulator to work, they are
    needed for making sure that the RESETTING, CLOCKING, and RUNNING signals
    are processed properly.
    There is also quite a bit of debugging code which gets added/removed
    ahead of this commit.
2024-11-10 Make the final changes needed to get the Reset Circuit working
2024-11-16 Organize the 74HC00 gates better
    Make better use of the NAND gates in the layout to make it easier for
    wiring on breadboard and PCB.
    * Closes #194
2024-11-17 Relocate the unused gates for efficiency
2024-12-03 Clean up the silkscreen on the Control ROM Module
    This includes a footprint update, moving some labels around, and adding
    a desription for the PCB.
2024-12-04 Remove the LEDs from the Control ROM Control Module
    The LEDs are not populated on the first iteration PCB. Remove them from
    the schematic and from the PCB design.
2024-12-05 Resolve the Control ROM Control pin alignment
    This resulted in a major change to the PCB layout.
2024-12-06 Rename RESET_CLK
    This also forces a rename of the SYSCLK on the Reset Schematic to be
    HS_CLK. The new name of the RESET_CLK is SYS_CLK.
2024-12-25 Look at the MAX704 uProcessor Supervisor
    This commit adds the documentation for the MAX704 supervisor. Some
    minor update in teh Control Rom Control circuit are added as well.
    Closes #198
2024-12-31 Update the Clock Module schematics
    This is what I hope will be the final incarnation of the clock module,
    making it all the way to the final build.
2025-01-06 Redo the Clock Module to conform to the new design
    This new design contains 3 oscillators:
    * High Speed oscillator, divided
    * Adjustable oscillator
    * Manual single step
2025-01-23 Schematic changes for clock and control ROM
2025-02-02 Some KiCad Cleanup
